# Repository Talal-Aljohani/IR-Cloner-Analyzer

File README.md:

# IR Cloner & Analyzer

**EE 3521 · Signals and Systems — Islamic University of Madinah**

A handheld device that captures the signal of any infrared remote, analyzes it with the tools of the course
(sampling, convolution, Fourier series, the DFT, the Z-transform) and sends it again in place of the original remote.

**Team:** Talal Aljohani · Saad Obaid · Moatasim Ahmad · Yousef Ahmed<br>
**Supervisor:** Dr. Abdulmajeed Alenezi

---

## Where the course is in the code

The firmware is 3,746 lines, but most of it is the touch screen, the menus, storage and the battery.
The signal processing that belongs to the course is in a few short places. Each link opens the exact lines.

| Step | Chapter | What it does | Code |
|---|---|---|---|
| 1. Sampling | Ch. 1 | x[n] = y(nTs), fs = 200 kSa/s, ω0Ts = 0.38π < π (no aliasing) | [`config.h:31`](firmware/IR_Cloner/config.h#L31), [`adc_stream.cpp:51`](firmware/IR_Cloner/adc_stream.cpp#L51) |
| 2. Envelope | Ch. 2, 10 | Max of every 50 µs window removes the carrier; ambient light tracked by y[n] = (31/32)y[n−1] + (1/32)x[n] | [`ir_rx.cpp:145-149`](firmware/IR_Cloner/ir_rx.cpp#L145-L149), [`ir_rx.cpp:83`](firmware/IR_Cloner/ir_rx.cpp#L83) |
| 3. Mark / space and durations | Ch. 2 | Threshold decision; the sensor's convolution stretches marks and shortens spaces | [`ir_rx.cpp:102`](firmware/IR_Cloner/ir_rx.cpp#L102), [`ir_rx.cpp:107-108`](firmware/IR_Cloner/ir_rx.cpp#L107-L108) |
| 4. Carrier frequency | Ch. 3, 5 | Square-wave Fourier series (a₁ at f0); Hann window + FFT (= DFT), peak between 25 and 60 kHz | [`dsp.cpp:47-54`](firmware/IR_Cloner/dsp.cpp#L47-L54), [`ir_rx.cpp:240`](firmware/IR_Cloner/ir_rx.cpp#L240) |
| 5. NEC decoding | logic, Ch. 2 | Each bit read from mark + space (the sum is not changed by the convolution); inverse-byte check | [`ir_decode.cpp:50-52`](firmware/IR_Cloner/ir_decode.cpp#L50-L52), [`ir_decode.cpp:56`](firmware/IR_Cloner/ir_decode.cpp#L56) |
| 6. Transmit | Ch. 1, 2 | Remove the convolution stretch, then the RMT builds x(t) = m(t)·c(t) | [`ir_decode.cpp:171-174`](firmware/IR_Cloner/ir_decode.cpp#L171-L174), [`ir_tx.cpp:15`](firmware/IR_Cloner/ir_tx.cpp#L15), [`ir_tx.cpp:44`](firmware/IR_Cloner/ir_tx.cpp#L44) |
| Math screen: RC | Ch. 2, 4 | RC = (t₂ − t₁)/ln 9 from the 90 %→10 % fall; H(jω) = 1/(1 + jωRC) | [`app.cpp:1074`](firmware/IR_Cloner/app.cpp#L1074) |
| Math screen: Z | Ch. 2, 5, 10 | y[n] = a·y[n−1] + (1−a)·x[n], H(z) = (1−a)/(1 − a z⁻¹), pole a = 0.905 (stable) | [`app.cpp:1209`](firmware/IR_Cloner/app.cpp#L1209), [`app.cpp:1169`](firmware/IR_Cloner/app.cpp#L1169) |

All of these steps are also collected in one short, commented file that runs on any PC:
[`firmware/Signals_Core.cpp`](firmware/Signals_Core.cpp). It runs the whole chain on a simulated remote press and prints
each result (`g++ -O2 -o core Signals_Core.cpp && ./core`).

## How it works

1. **Sampling (Ch. 1).** The photodiode turns the IR light into a voltage y(t). The ESP32 ADC samples it at
   200 kSa/s (Ts = 5 µs) through DMA. The 38 kHz carrier becomes ω0Ts = 0.38π < π, so there is no aliasing;
   at 50 kSa/s it would be 1.52π and show up as 12 kHz (shown on the Experiment screen).
2. **Envelope (Ch. 2, 10).** The maximum of every 10 samples (50 µs, longer than one 26 µs carrier period)
   removes the carrier ripple. Ambient light is followed by a first-order low-pass difference equation and subtracted.
3. **Mark / space (Ch. 2).** A threshold turns the envelope into marks and spaces; their durations are the message m(t).
   The sensor is a slow LTI system, h(t) = (1/RC)·e^(−t/RC): the convolution makes every mark longer and the next space shorter.
4. **Carrier (Ch. 3, 5).** 1024 samples from inside the first mark, Hann window, FFT; the highest peak between
   25 and 60 kHz is the carrier (a₁ of the square wave, 38.00 kHz on our remotes). Bin width fs/N = 195 Hz.
5. **NEC decoding.** Each bit is read from mark + space (1.125 ms = 0, 2.25 ms = 1), so the convolution stretch cancels.
   Other protocols are kept as raw timings.
6. **Transmit (Ch. 1).** The stretch is removed, then the ESP32 RMT peripheral rebuilds x(t) = m(t)·c(t) with the
   measured carrier and a 1/3 duty cycle, and drives three IR LEDs through a 2N2222 transistor.

The **Math** screen applies the course to your own capture: it measures the sensor RC from the 90 %→10 % fall
(≈ 61 µs on our board), plots |H(jω)|, and runs y[n] = a·y[n−1] + (1−a)·x[n] with its pole on the z-plane.

## Hardware guide

[**Hardware Guide (PDF)**](docs/Hardware_Guide.pdf): a step-by-step build manual, one step per page with the parts and where they go:
the two circuits, the IR board (KiCad design, laser cutting, every part in order), version 1 and the redesign around the CYD board,
the case assembly, and the first power-on.

## Repository layout

```
firmware/
  IR_Cloner/          Arduino sketch for the ESP32 (open IR_Cloner.ino)
    config.h          all constants: sample rate, window, pins, carrier
    adc_stream.cpp    step 1: 200 kSa/s ADC with DMA
    ir_rx.cpp         steps 2-3: envelope, mark/space, durations, carrier estimate
    dsp.cpp           step 4: Hann window, FFT, peak, aliasing
    ir_decode.cpp     step 5: NEC decoding, timing correction before sending
    ir_tx.cpp         step 6: x = m * c with the RMT peripheral
    app.cpp           screens and menus (Math screen: fitRc, Z page)
    touch_xpt2046.cpp, storage.cpp, power.cpp   touch, saved signals, battery (not course material)
  Signals_Core.cpp    the whole signal chain in one PC program, for study
  tools/plot_capture.m  MATLAB script: plot a raw ADC dump (time signal + spectrum)
hardware/
  ir_board/           KiCad 10 project of the IR board (receiver + 3 LEDs), with fab files (schematic, BOM, gerbers)
  case/               3D-printed case (STL) and the Autodesk Fusion script that builds it
docs/                 Hardware_Guide.pdf
images/               pictures used in this README
```

## Hardware

- **Main board:** lcdwiki E32R28T "Cheap Yellow Display" (CYD) (ESP32 + 2.8 in ILI9341 touch screen + battery charger).
- **IR board (ours):** photodiode receiver on GPIO35 (ADC1 channel 7) and three IR LEDs driven by a 2N2222 on GPIO27.

The first version used our own main board with an ESP32 module, a separate display, a charger and a boost converter (six modules, 31 wires). The final version uses one CYD board plus our IR board
(old on the left, new on the right):

## Building the firmware

| Setting | Value |
|---|---|
| Board package | esp32 by Espressif, version 3.x (tested on 3.3.11) |
| Board | ESP32 Dev Module |
| Partition scheme | Default 4MB with spiffs |
| Libraries | Adafruit ILI9341, Adafruit GFX, Adafruit BusIO |

Open `firmware/IR_Cloner/IR_Cloner.ino` in the Arduino IDE and upload. The FFT and the touch driver are written inside the
project, so no other libraries are needed. Serial Monitor at 115200 shows the measured ADC rate at start-up.

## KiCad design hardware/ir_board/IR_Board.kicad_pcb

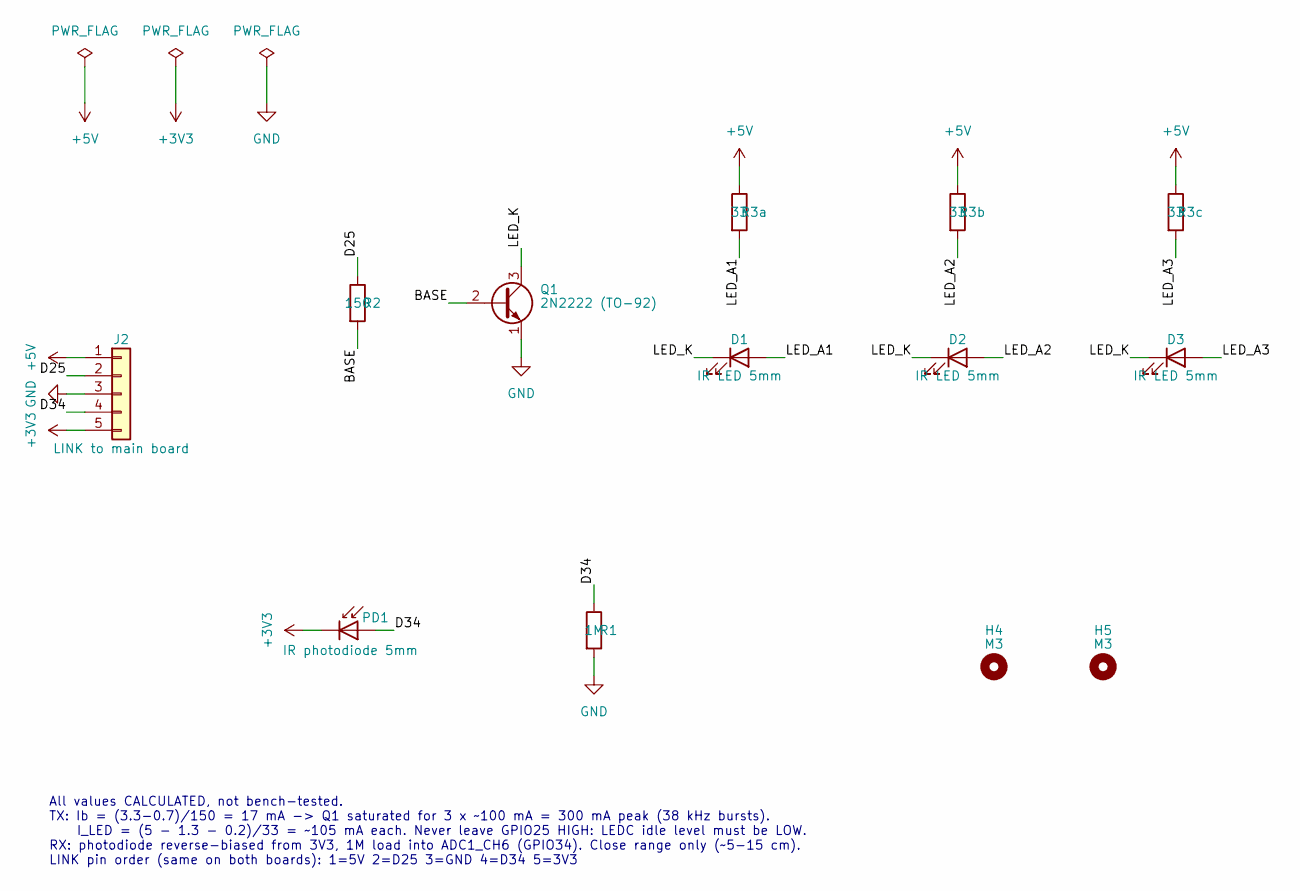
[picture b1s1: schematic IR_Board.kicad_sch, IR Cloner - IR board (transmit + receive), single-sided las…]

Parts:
D1, D2, D3: IR LED 5mm; SS_LED_D5.0mm
H4, H5: M3; SS_MountingHole_M3
J2: LINK to main board; SS_Link_1x05_P2.54
PD1: IR photodiode 5mm; SS_PD_D5.0mm
Q1: 2N2222 (TO-92); SS_TO-92_Wide
R1: 1M; SS_R_Axial_P7.62
R2: 150; SS_R_Axial_P7.62
R3a, R3b, R3c: 33; SS_R_Axial_P7.62

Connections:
+3V3: J2.5, PD1.1 (K)
+5V: J2.1, R3a.1, R3b.1, R3c.1
/BASE: Q1.2 (B), R2.2
/D25: J2.2, R2.1
/D34: J2.4, PD1.2 (A), R1.1
/LED_A1: D1.2 (A), R3a.2
/LED_A2: D2.2 (A), R3b.2
/LED_A3: D3.2 (A), R3c.2
/LED_K: D1.1 (K), D2.1 (K), D3.1 (K), Q1.3 (C)
GND: J2.3, Q1.1 (E), R1.2

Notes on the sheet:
All values CALCULATED, not bench-tested. TX: Ib = (3.3-0.7)/150 = 17 mA -> Q1 saturated for 3 x ~100 mA = 300 mA peak (38 kHz bursts). I_LED = (5 - 1.3 - 0.2)/33 = ~105 mA each. Never leave GPIO25 HIGH: LEDC idle level must be LOW. RX: photodiode reverse-biased from 3V3, 1M load into ADC1_CH6 (GPIO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

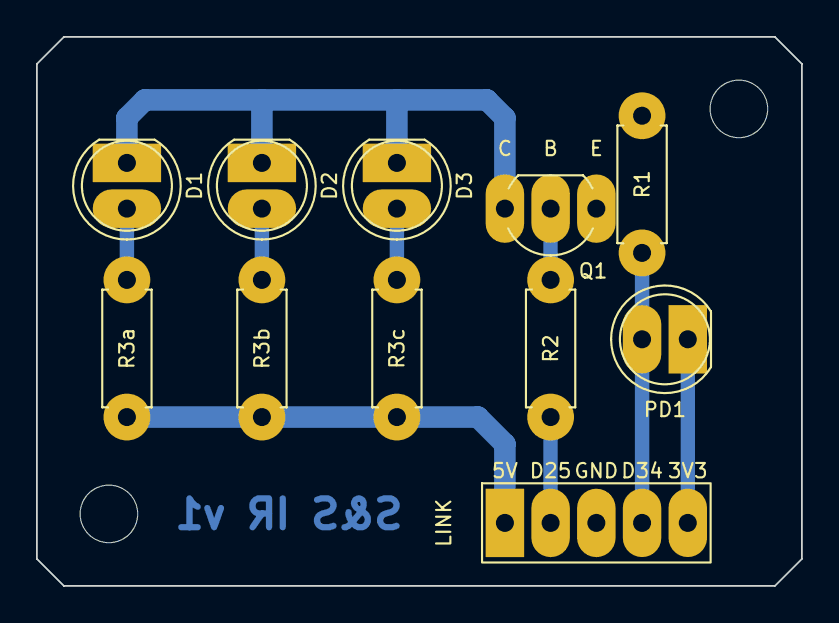
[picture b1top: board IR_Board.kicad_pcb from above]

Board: 2 copper layers, 42.5 x 30.5 mm, 13 parts (0 on the bottom side), 10 nets.
